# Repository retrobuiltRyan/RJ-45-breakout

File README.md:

# RJ-45-breakout
Screw terminal breakout board for rJ-45 connectors and cables. A beginner KiCAD learning project. The project files are incomplete- open with KiCAD; follow the to-do list in the schematic and board layout. Attempt to complete the project.

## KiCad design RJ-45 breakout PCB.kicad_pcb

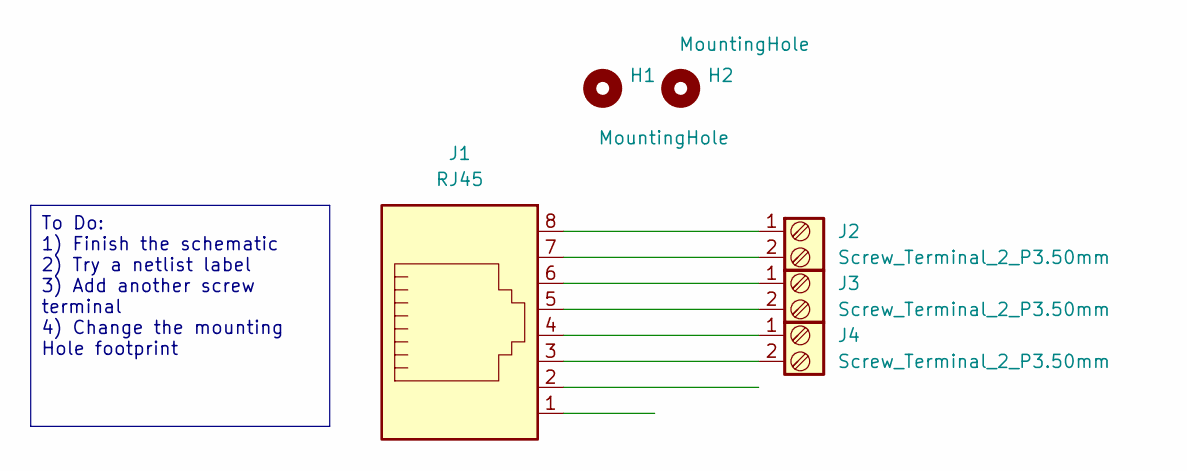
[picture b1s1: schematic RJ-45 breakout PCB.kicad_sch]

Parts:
H1, H2: MountingHole; MountingHole_4.3mm_M4
J1: RJ45; RJ45_Amphenol_54602-x08_Horizontal; DigiKey P/N 609-1046-ND
J2, J3, J4: Screw_Terminal_2_P3.50mm; TerminalBlock_Phoenix_PT-1,5-2-3.5-H_1x02_P3.50mm_Horizontal; DigiKey P/N 732-2747-ND

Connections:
unnamed: J1.3, J4.2
unnamed: J1.4, J4.1
unnamed: J1.5, J3.2
unnamed: J1.6, J3.1
unnamed: J1.7, J2.2
unnamed: J1.8, J2.1

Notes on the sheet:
To Do: 1) Finish the schematic 2) Try a netlist label 3) Add another screw terminal 4) Change the mounting Hole footprint

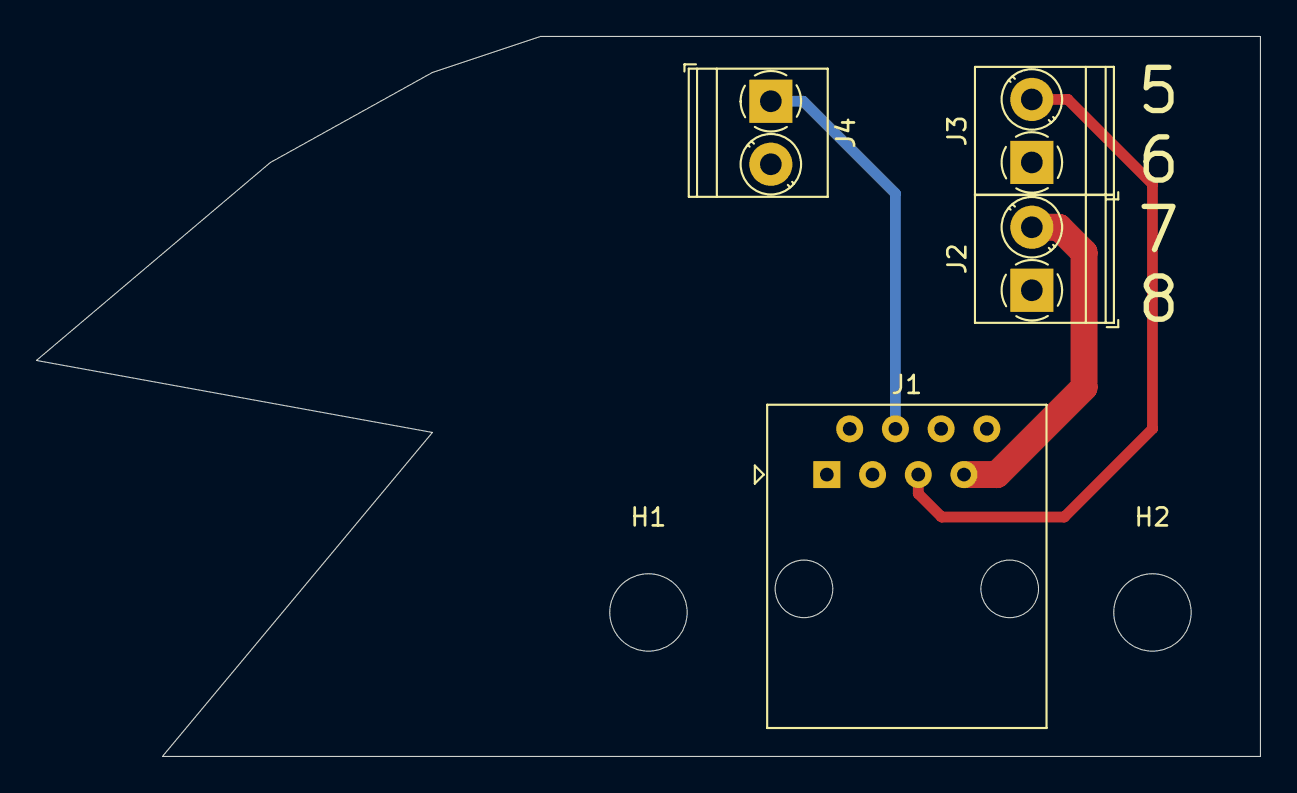
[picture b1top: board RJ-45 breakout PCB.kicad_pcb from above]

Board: 2 copper layers, 68.0 x 40.0 mm, 6 parts (0 on the bottom side), 6 nets.

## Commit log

2026-06-01 kicad_files/RJ-45 breakout PCB
    KiCAD project, PCB, and schematic files. Place in a folder of the same name and open project file with KiCAD v10 or newer.
